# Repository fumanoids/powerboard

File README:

README FOR THE POWER BOARD HARD- AND SOFTWARE RELEASE
           =====================================================

          2016-01-11 FUmanoids' Powerboard Hardware Release v2016

          Copyright (c) 2016 FUmanoids / Freie Universität Berlin
                            All rights reserved

        For full license information, please refer to file LICENCE

Links:
       FUmanoids Homepage                           http://www.fumanoids.de
       FUmanoids on Facebook              http://www.facebook.com/fumanoids
       FUmanoids on Twitter                    http://twitter.com/fumanoids

       RoboCup Homepage                              http://www.robocup.org
       RoboCup Humanoid League Homepage          http://www.tzi.de/humanoid

This is part of the code/hardware release of team FUmanoids, version 2016. 

Our goal by releasing the source code and CAD files of components of our robot
is to provide some insight in humanoid soccer robot development, allowing other
teams to learn from our code and possibly our mistakes, but also to hopefully
encourage them to do the same and release their code as well. Though RoboCup is
a competition, it's also about research and finally to achieve our common goal -
to win against FIFA in 2050 ...

 1. PROJECT STRUCTURE
----------------------

The FUmanoids team has developed several software applications as well as our
own robots. The latter was developed internally and equipped with both
commercially available and self-built electronics.

This release addresses only the custom-built power board used in the FUmanoid
robots.

Neither a compiler, an SDK or CAD software is part of this package. In the
section "Getting Started" you find a list of recommended software to modify or
view the CAD files, to compile the software and to put the binaries onto the
processors.

 1.1 Overview of the package
-----------------------------

The project's root directory is "powerboard" (the board's name).

The directories in the root directory are:

 - bin      -- some useful scripts and programs for building the program and
               documentation
 - obj      -- All binary files of the program go here. This directory will
               be created during code compilation.
 - doc      -- The documentation directory. Here you can find some 
               documentation of the board.
 - src      -- The actual source code.
               Note: The essential parts of the software is pretty well
               documented. Please consider this as a documentation 
               directory as well.
 - hardware -- Here you can find the CAD files for the PCB.

 2. THE POWERBOARD PROJECT
------------------------- 

 2.1 Getting Started
-------------------------

 2.1.1 Software

The software is written in C with two extensions in assembler
(system_mutex_lock() and system_mutex_unlock()).

A compiler for the target hardware is not part of this package but can be picked
based on the user's preferences. We recommend using the arm-none-eabi-toolchain
(including gcc, ld and gdb) which can be found here:

                  https://launchpad.net/gcc-arm-embedded/+download

 2.1.2 Hardware

To view the schematics and layout of this project we recommend using "CadSoft
EAGLE" which can be found at: http://www.cadsoftusa.com/

 2.1.3 Manufacturing

The PCB can be manufactured by most commonly known PCB services. A partlist can
be found in the folder where the schematics reside. But please double check the 
partlist since we cannot guarantee its completeness.

We chose every component on the board to be manually solderable. All you need is
a steady hand. And preferably a rework station.

 2.1.4 Other Prerequisites
 
To flash the target an ARM compatible JTAG is needed.

We recommend using an "JLink" from Segger.
There is numerous software available for all major operating systems supporting
the programmer (Linux, Mac, Windows). 

 2.2 Compiling the Software
---------------------------

To compile for debug run: make
To build a release build: RELEASE=1 make

The common IDE used for development in team FUmanoids is Eclipse/CDT which
is available at http://www.eclipse.org. Therefore we have the corresponding
project files added to our repository, to give an easy start. You can build the
code either by using Eclipse or by shell tools. Both ways are easy.
Other IDEs or editors can of course be used.

The build process generates a .elf file which can be flashed on the target.

 2.2.1 Using Eclipse

If you choose to use Eclipse click File->Import and in the opening window
General->"Existing Project into Workspace" and choose the project's root
directory. Then you can compile the debug or release version of the software.

 2.2.2 Using the shell tools

You can simply run

 make

to compile the code.

 2.3 Flashing the target
------------------------

In order to flash the target you need an JTAG. We recommend using the 
Segger/JLink software to communicate with the JTAG and as tool to download 
code onto the target.

If you have JLinkGDBServer installed you can use 

JLinkGDBServer -if swd
make flash 

to flash the target.

 4. REFERENCES
--------------

The framework used in this software was developed as part of the FUmanoid
project and is used in it's sensor board as well (the project can be found
at http://www.fumanoids.de/hardware/erolf). The Berlin United Racing Team
incorporates a microcontroller board similar to the power board which is
operated by the framework as well.

Many aspects of our work is described in the corresponding theses of our
students, which are available online at http://www.fumanoids.de/publications,
though most of them are in German.

 5. CONTACT
-----------

We'd love to receive feedback, please feel free to contact us by email
at info@fumanoids.de. For information about our team and ongoing progress,
follow us on https://www.facebook.com/fumanoids, https://twitter.com/fumanoids
and http://www.fumanoids.de.

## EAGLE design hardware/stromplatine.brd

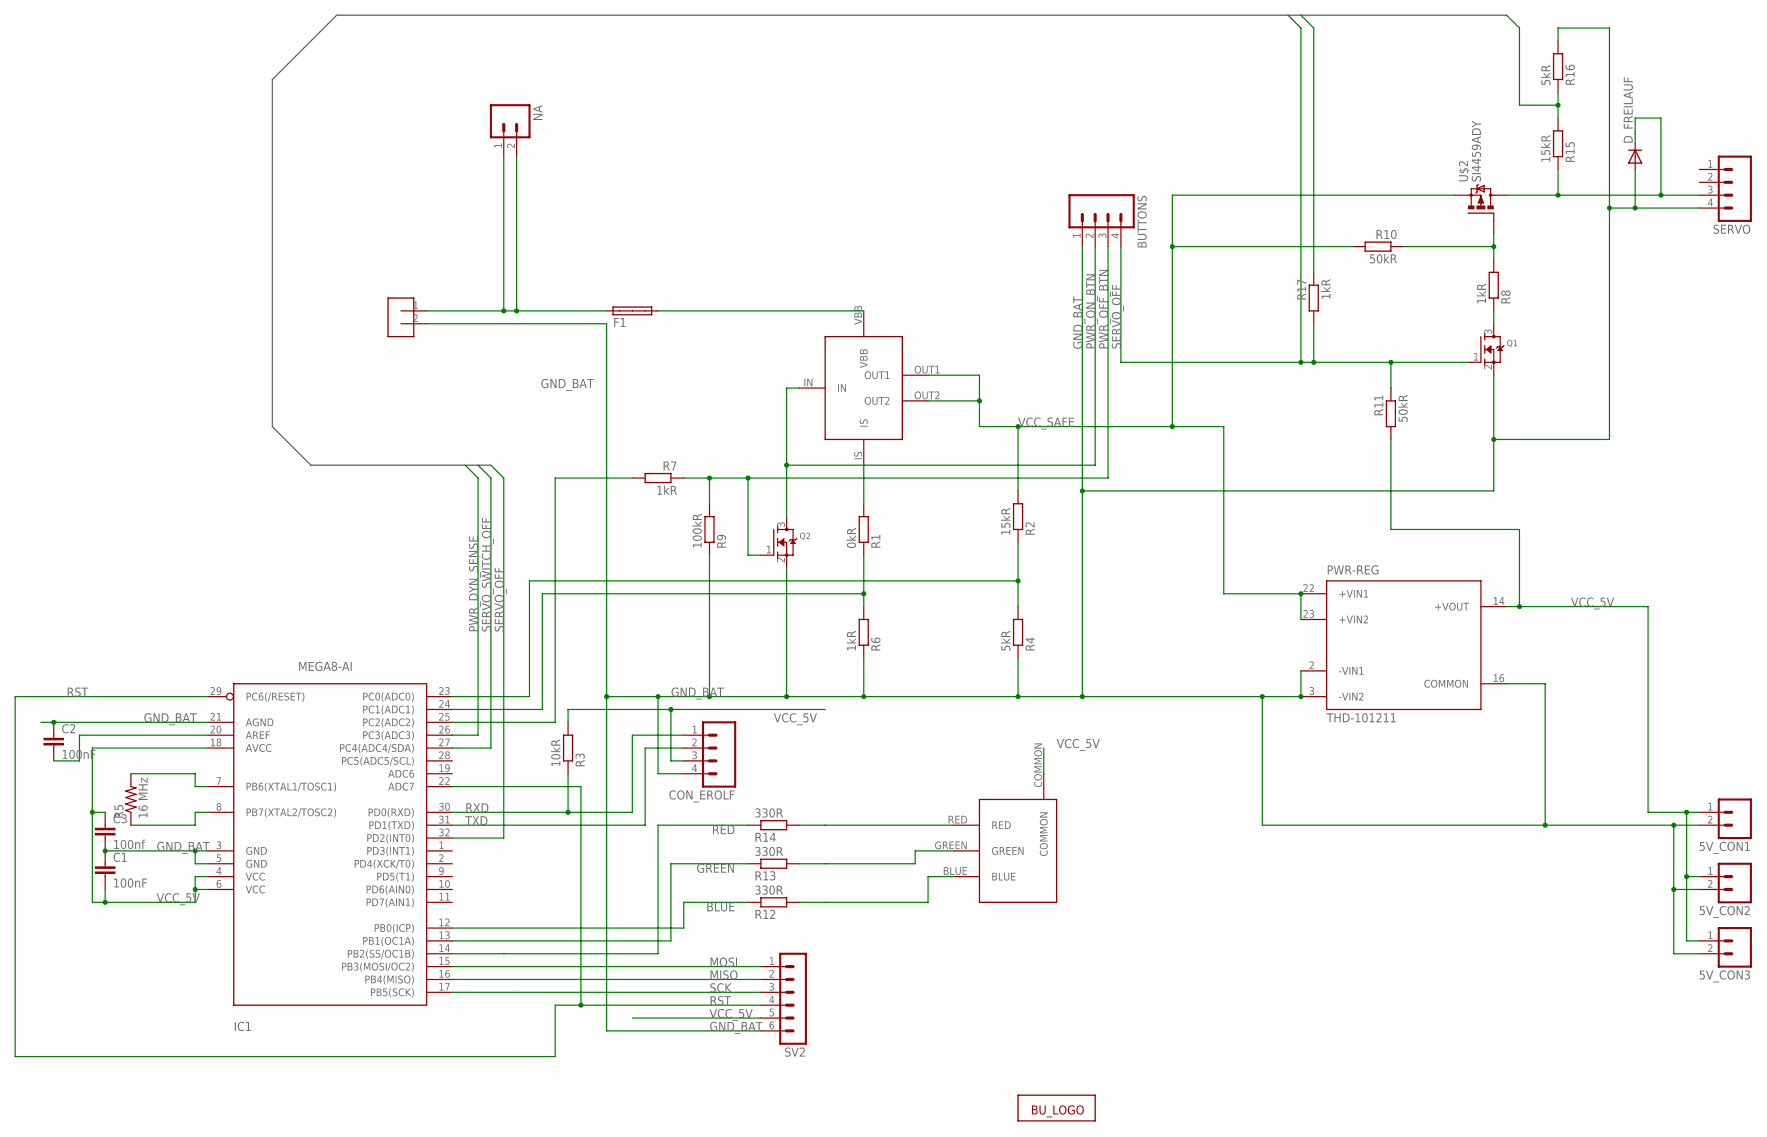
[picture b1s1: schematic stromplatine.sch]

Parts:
5V_CON1, 5V_CON2, 5V_CON3: M02; 02P
BUTTONS: M04; 04P
C1, C2: 100nF; C0805
C3: 100nf; C0805
CON_BAT: STROMSTECKER
CON_EROLF: M04; 04P
D_FREILAUF: DIODE-DO-214AC; DO-214AC
F1: SHK20Q
IC1: MEGA8-AI; TQFP32-08
NA: M02; 02P
PWR-REG: THD-101211; TEN3XXXX
Q1, Q2: MOSFET-NREFLOW; SOT23
R1: 0kR; M0805
R2, R15: 15kR; M0805
R3: 10kR; M0805
R4, R16: 5kR; M0805
R5: 16 MHz; MINI_MELF-0102W
R6, R7, R8, R17: 1kR; M0805
R9: 100kR; M0805
R10, R11: 50kR; M0805
R12, R13, R14: 330R; M0805
SERVO: M04; 04P
SV2: MA06-1
U$1: BTS555; PG-TO218
U$2: SI4459ADY; SO-8
U$3: RGB-LED; 4-PLCC
U$4: LOGO

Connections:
BLUE: IC1.12 (PB0(ICP)), R12.1
GND_BAT: 5V_CON1.2, 5V_CON2.2, 5V_CON3.2, BUTTONS.1, C1.1, C2.1, C3.2, CON_BAT.2, CON_EROLF.4, D_FREILAUF.A, IC1.3 (GND), IC1.5 (GND), IC1.21 (AGND), PWR-REG.2 (-VIN1), PWR-REG.3 (-VIN2), PWR-REG.16 (COMMON), Q1.2 (S), Q2.2 (S), R4.1, R6.1, R9.1, R16.2, SERVO.4, SV2.6
GREEN: IC1.13 (PB1(OC1A)), R13.1
MISO: IC1.16 (PB4(MISO)), SV2.2
MOSI: IC1.15 (PB3(MOSI/OC2)), SV2.1
unnamed: F1.2A, U$1.VBB
unnamed: CON_BAT.1, F1.1A, NA.1, NA.2
unnamed: IC1.7 (PB6(XTAL1/TOSC1)), R5.2
unnamed: R12.2, U$3.BLUE
unnamed: R13.2, U$3.GREEN
unnamed: IC1.8 (PB7(XTAL2/TOSC2)), R5.1
unnamed: IC1.23 (PC0(ADC0)), R2.1, R4.2
unnamed: D_FREILAUF.C, R15.1, SERVO.3, U$2.P5 (D), U$2.P6 (D), U$2.P7 (D), U$2.P8 (D)
unnamed: C2.2, IC1.20 (AREF)
unnamed: R8.2, R10.1, U$2.P4 (G)
unnamed: IC1.24 (PC1(ADC1)), R1.1, R6.2
unnamed: R1.2, U$1.IS
unnamed: Q1.3 (D), R8.1
unnamed: R14.2, U$3.RED
unnamed: IC1.25 (PC2(ADC2)), R7.2
PWR_DYN_SENSE: IC1.26 (PC3(ADC3)), R15.2, R16.1
PWR_OFF_BTN: BUTTONS.3, Q2.1 (G), R7.1, R9.2
PWR_ON_BTN: BUTTONS.2, Q2.3 (D), U$1.IN
RED: IC1.14 (PB2(SS/OC1B)), R14.1
RST: IC1.22 (ADC7), IC1.29 (PC6(/RESET)), SV2.4
RXD: CON_EROLF.1, IC1.30 (PD0(RXD)), R3.1
SCK: IC1.17 (PB5(SCK)), SV2.3
SERVO_OFF: BUTTONS.4, IC1.32 (PD2(INT0)), Q1.1 (G), R11.1, R17.2
SERVO_SWITCH_OFF: IC1.27 (PC4(ADC4/SDA)), R17.1
TXD: CON_EROLF.2, IC1.31 (PD1(TXD))
VCC_5V: 5V_CON1.1, 5V_CON2.1, 5V_CON3.1, C1.2, C3.1, CON_EROLF.3, IC1.4 (VCC), IC1.6 (VCC), IC1.18 (AVCC), PWR-REG.14 (+VOUT), R3.2, R11.2, SV2.5, U$3.COMMON
VCC_SAFE: PWR-REG.22 (+VIN1), PWR-REG.23 (+VIN2), R2.2, R10.2, U$1.OUT1, U$1.OUT2, U$2.P1 (S), U$2.P2 (S), U$2.P3 (S)

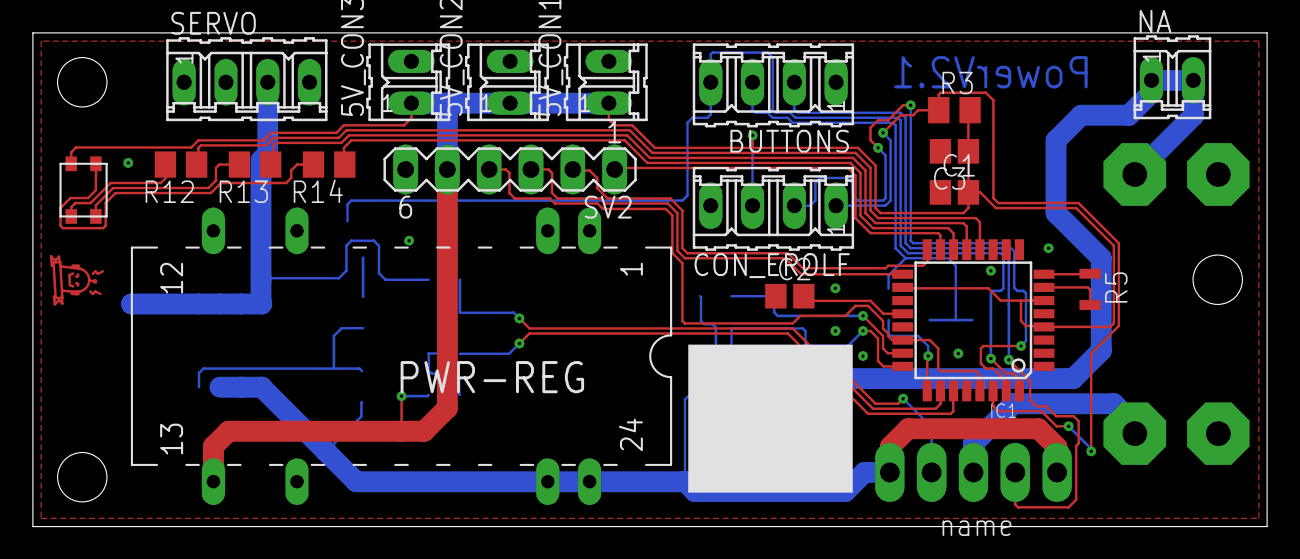
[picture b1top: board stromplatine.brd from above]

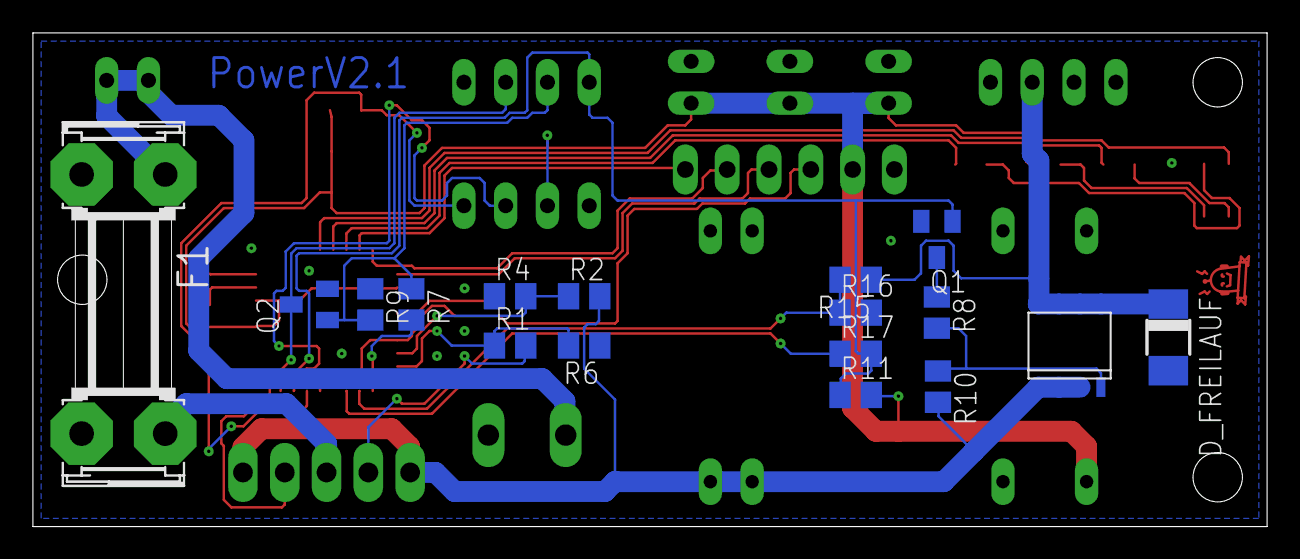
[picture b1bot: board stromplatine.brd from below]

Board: 2 copper layers, 75.0 x 30.0 mm, 39 parts (17 on the bottom side), 32 nets.

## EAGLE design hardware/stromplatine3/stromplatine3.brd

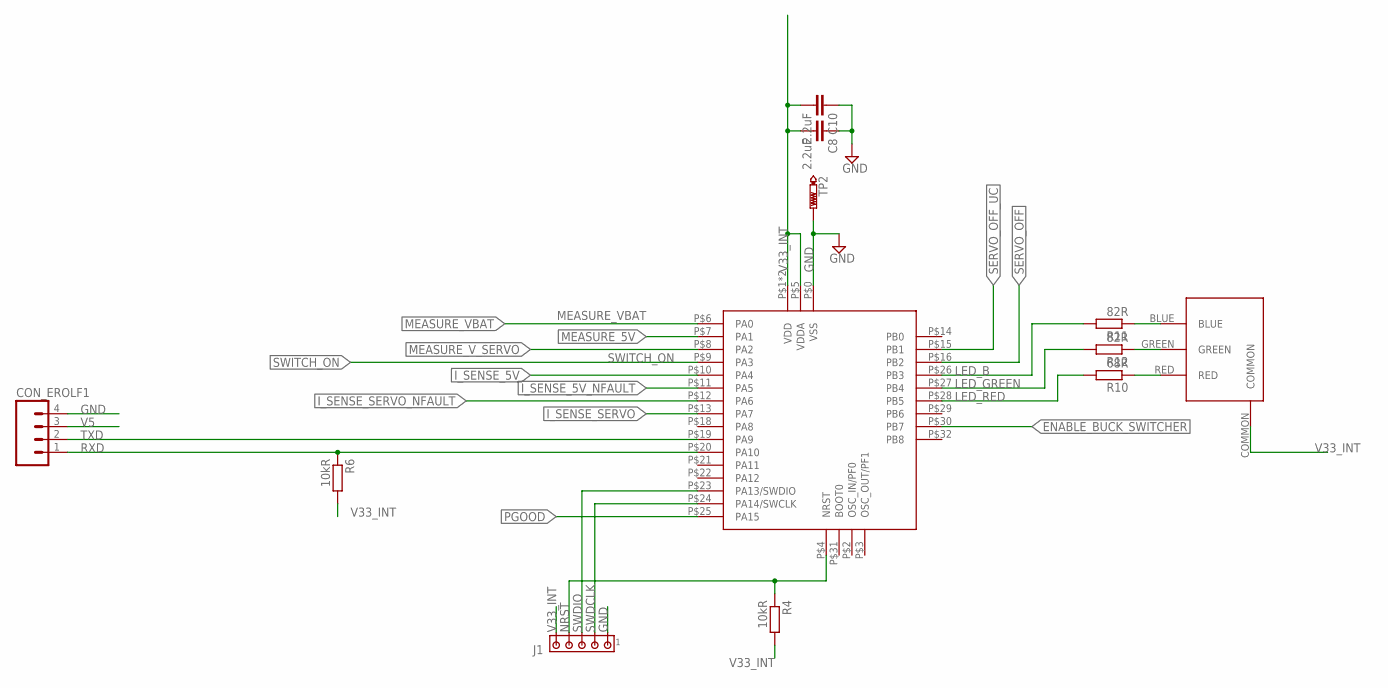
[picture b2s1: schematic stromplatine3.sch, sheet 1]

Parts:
C8, C10: 2.2uF; C0402
CON_EROLF1: M04; 04P
J1: MTA05-100; 10X05MTA
R4, R6: 10kR; R0603
R10: 68R; R0603
R11, R12: 82R; R0603
TP2: PTR1B1,27; B1,27
U$1: STM32F051K8; UFQFPN32
U$3: RGB-LED; 4-PLCC

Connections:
ENABLE_BUCK_SWITCHER: U$1.P$30 (PB7); also elsewhere on the board
GND: C8.1, C10.1, CON_EROLF1.4, J1.1, TP2.TP, U$1.P$0 (VSS); also elsewhere on the board
I_SENSE_5V: U$1.P$10 (PA4); also elsewhere on the board
I_SENSE_5V_NFAULT: U$1.P$11 (PA5); also elsewhere on the board
I_SENSE_SERVO: U$1.P$13 (PA7); also elsewhere on the board
I_SENSE_SERVO_NFAULT: U$1.P$12 (PA6); also elsewhere on the board
LED_B: R11.2, U$1.P$26 (PB3)
LED_GREEN: R12.2, U$1.P$27 (PB4)
LED_RED: R10.2, U$1.P$28 (PB5)
MEASURE_5V: U$1.P$7 (PA1); also elsewhere on the board
MEASURE_VBAT: U$1.P$6 (PA0); also elsewhere on the board
MEASURE_V_SERVO: U$1.P$8 (PA2); also elsewhere on the board
unnamed: R10.1, U$3.RED
unnamed: R12.1, U$3.GREEN
unnamed: R11.1, U$3.BLUE
NRST: J1.4, R4.1, U$1.P$4 (NRST)
PGOOD: U$1.P$25 (PA15)
RXD: CON_EROLF1.1, R6.1, U$1.P$20 (PA10)
SERVO_OFF: U$1.P$16 (PB2); also elsewhere on the board
SERVO_OFF_UC: U$1.P$15 (PB1)
SWDCLK: J1.2, U$1.P$24 (PA14/SWCLK)
SWDIO: J1.3, U$1.P$23 (PA13/SWDIO)
SWITCH_ON: U$1.P$9 (PA3); also elsewhere on the board
TXD: CON_EROLF1.2, U$1.P$19 (PA9)
V5: CON_EROLF1.3; also elsewhere on the board
V33_INT: C8.2, C10.2, J1.5, R4.2, R6.2, U$1.P$1 (VDD), U$1.P$5 (VDDA), U$1.P$17 (VDD), U$3.COMMON; also elsewhere on the board

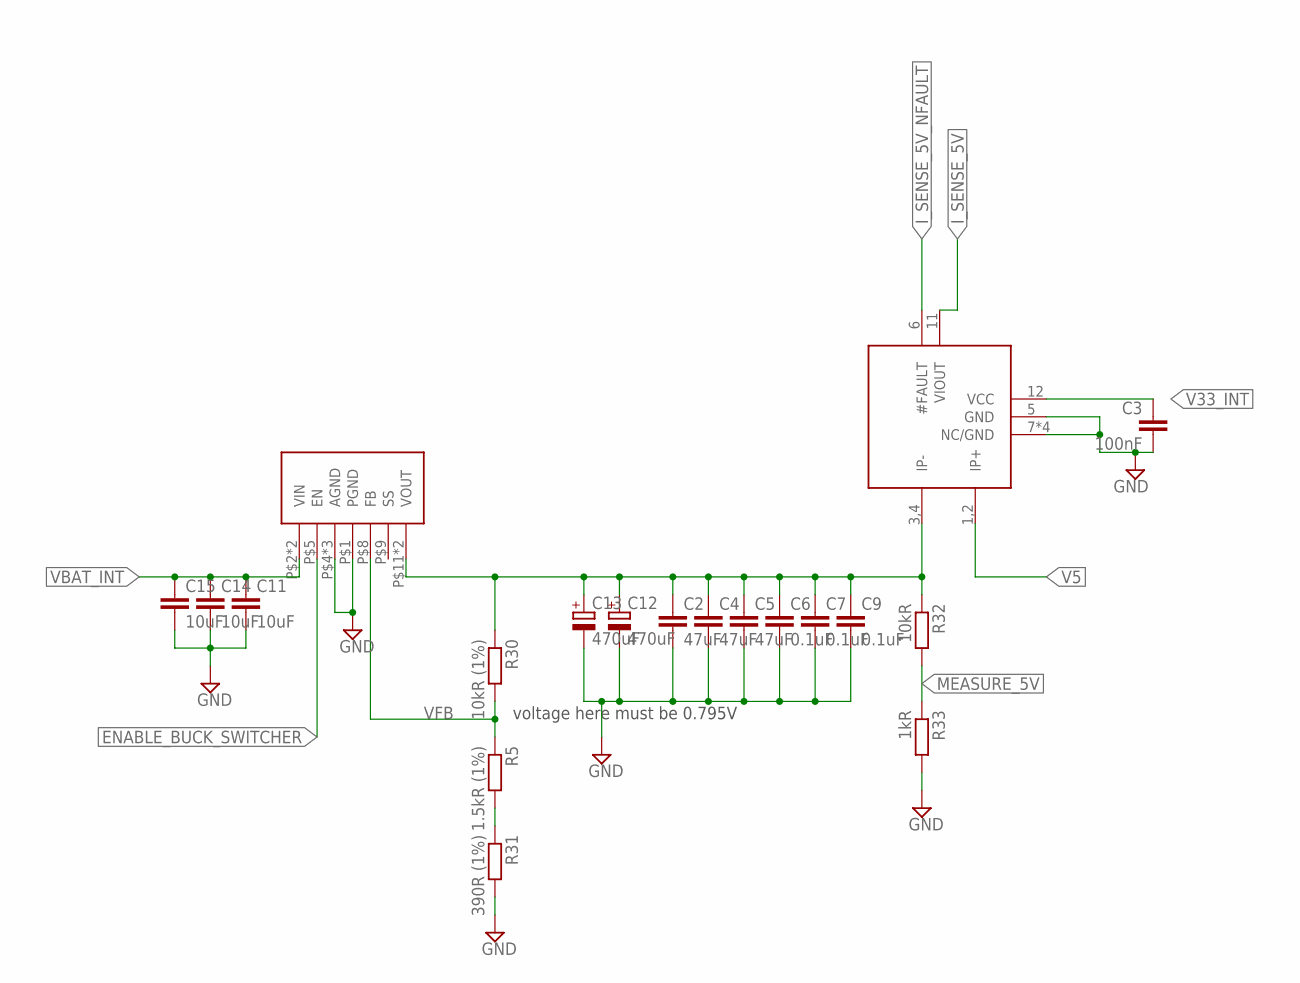
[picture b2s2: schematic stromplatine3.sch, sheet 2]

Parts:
C2, C4, C5: 47uF; C1206
C3: 100nF; C0402
C6, C7, C9: 0.1uF; C0603
C11, C14, C15: 10uF; C1206; DIGIKEY 587-1353-1-ND
C12, C13: 470uF; 175TMP-0810; DIGIKEY 493-3771-1-ND
R5: 1.5kR (1%); R0603
R30: 10kR (1%); R0603
R31: 390R (1%); R0603
R32: 10kR; R0603
R33: 1kR; R0603
U$10: ACS711; QFN-12-EX
U$11: LMZ12010; TZA11A

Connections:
ENABLE_BUCK_SWITCHER: U$11.P$5 (EN); also elsewhere on the board
GND: C2.2, C3.2, C4.2, C5.2, C6.2, C7.2, C9.2, C11.2, C12.-, C13.-, C14.2, C15.2, R31.2, R33.2, U$10.5 (GND), U$10.7 (NC/GND), U$10.8 (NC/GND), U$10.9 (NC/GND), U$10.10 (NC/GND), U$11.P$1 (PGND), U$11.P$4 (AGND), U$11.P$6 (AGND), U$11.P$7 (AGND); also elsewhere on the board
I_SENSE_5V: U$10.11 (VIOUT); also elsewhere on the board
I_SENSE_5V_NFAULT: U$10.6 (#FAULT); also elsewhere on the board
MEASURE_5V: R32.2, R33.1; also elsewhere on the board
unnamed: R5.2, R31.1
unnamed: C2.1, C4.1, C5.1, C6.1, C7.1, C9.1, C12.+, C13.+, R30.1, R32.1, U$10.3,4 (IP-), U$11.P$11 (VOUT), U$11.P$12 (VOUT)
V5: U$10.1,2 (IP+); also elsewhere on the board
V33_INT: C3.1, U$10.12 (VCC); also elsewhere on the board
VBAT_INT: C11.1, C14.1, C15.1, U$11.P$2 (VIN), U$11.P$3 (VIN); also elsewhere on the board
VFB: R5.1, R30.2, U$11.P$8 (FB)

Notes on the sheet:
voltage here must be 0.795V

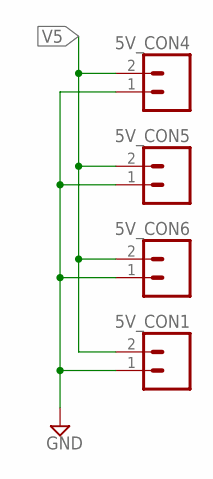
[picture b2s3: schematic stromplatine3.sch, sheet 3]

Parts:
5V_CON1, 5V_CON4, 5V_CON5, 5V_CON6: M02; 02P

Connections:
GND: 5V_CON1.1, 5V_CON4.1, 5V_CON5.1, 5V_CON6.1; also elsewhere on the board
V5: 5V_CON1.2, 5V_CON4.2, 5V_CON5.2, 5V_CON6.2; also elsewhere on the board

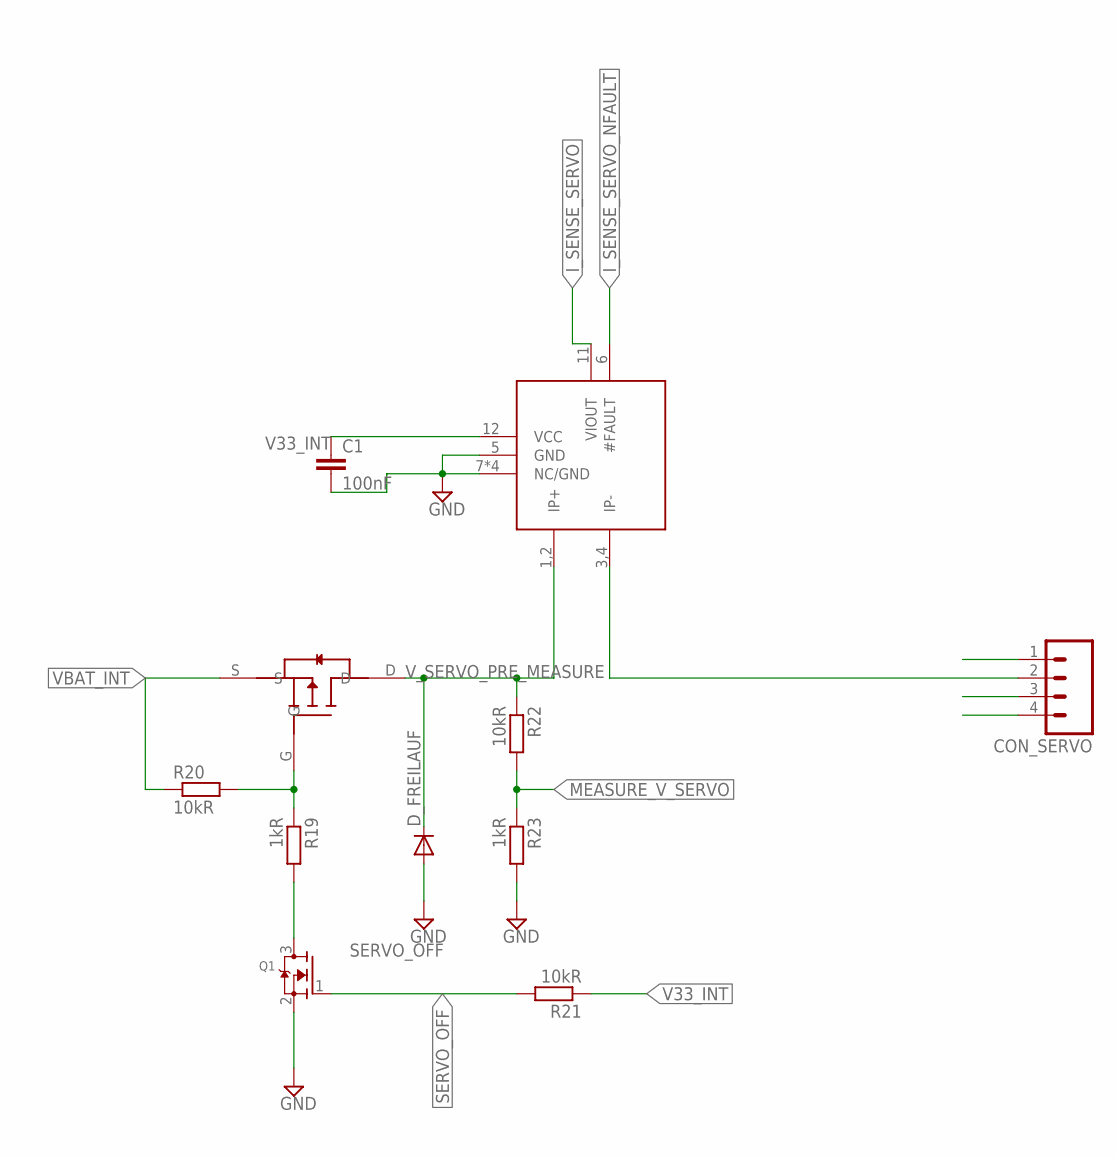
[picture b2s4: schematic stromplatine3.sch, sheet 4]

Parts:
C1: 100nF; C0402
CON_SERVO: M04; 04P
D_FREILAUF: DIODE-DO-214AC; DO-214AC
Q1: MOSFET-NREFLOW; SOT23
R19, R23: 1kR; R0603
R20, R21, R22: 10kR; R0603
U$6: ACS711; QFN-12-EX
U$7: MOSFET/AOD417; TO-252

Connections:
GND: C1.2, CON_SERVO.1, D_FREILAUF.A, Q1.2 (S), R23.2, U$6.5 (GND), U$6.7 (NC/GND), U$6.8 (NC/GND), U$6.9 (NC/GND), U$6.10 (NC/GND); also elsewhere on the board
I_SENSE_SERVO: U$6.11 (VIOUT); also elsewhere on the board
I_SENSE_SERVO_NFAULT: U$6.6 (#FAULT); also elsewhere on the board
MEASURE_V_SERVO: R22.2, R23.1; also elsewhere on the board
unnamed: Q1.3 (D), R19.2
unnamed: R19.1, R20.2, U$7.G
RS485_SERVO_A: CON_SERVO.3
RS485_SERVO_B: CON_SERVO.4
SERVO_OFF: Q1.1 (G), R21.2; also elsewhere on the board
V33_INT: C1.1, R21.1, U$6.12 (VCC); also elsewhere on the board
VBAT_INT: R20.1, U$7.S; also elsewhere on the board
V_SERVO: CON_SERVO.2, U$6.3,4 (IP-)
V_SERVO_PRE_MEASURE: D_FREILAUF.C, R22.1, U$6.1,2 (IP+), U$7.D

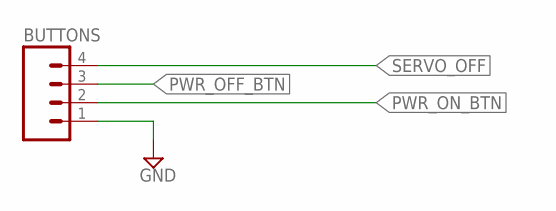
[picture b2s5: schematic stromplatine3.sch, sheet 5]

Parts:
BUTTONS: M04; 04P

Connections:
GND: BUTTONS.1; also elsewhere on the board
PWR_OFF_BTN: BUTTONS.3; also elsewhere on the board
PWR_ON_BTN: BUTTONS.2; also elsewhere on the board
SERVO_OFF: BUTTONS.4; also elsewhere on the board

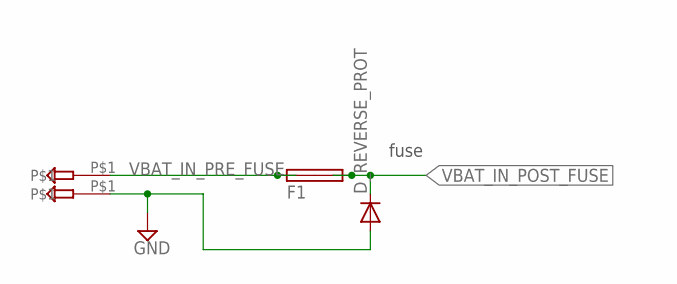
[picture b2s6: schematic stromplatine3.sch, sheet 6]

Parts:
D_REVERSE_PROT: DIODE-DO-214AC; DO-214AC
F1: SHK20Q
U$8, U$9: TP

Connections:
GND: D_REVERSE_PROT.A, U$9.P$1; also elsewhere on the board
VBAT_IN_POST_FUSE: D_REVERSE_PROT.C, F1.2A, F1.2B; also elsewhere on the board
VBAT_IN_PRE_FUSE: F1.1A, F1.1B, U$8.P$1

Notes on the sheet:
fuse

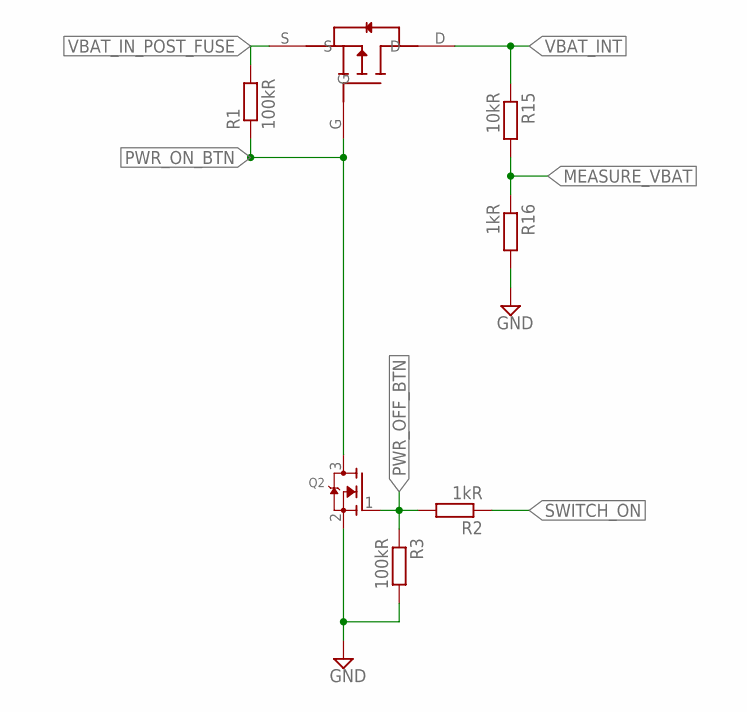
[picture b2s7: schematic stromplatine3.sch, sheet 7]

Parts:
Q2: MOSFET-NREFLOW; SOT23
R1, R3: 100kR; R0603
R2, R16: 1kR; R0603
R15: 10kR; R0603
U$4: MOSFET/AOD417; TO-252

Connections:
GND: Q2.2 (S), R3.2, R16.2; also elsewhere on the board
MEASURE_VBAT: R15.2, R16.1; also elsewhere on the board
PWR_OFF_BTN: Q2.1 (G), R2.2, R3.1; also elsewhere on the board
PWR_ON_BTN: Q2.3 (D), R1.1, U$4.G; also elsewhere on the board
SWITCH_ON: R2.1; also elsewhere on the board
VBAT_INT: R15.1, U$4.D; also elsewhere on the board
VBAT_IN_POST_FUSE: R1.2, U$4.S; also elsewhere on the board

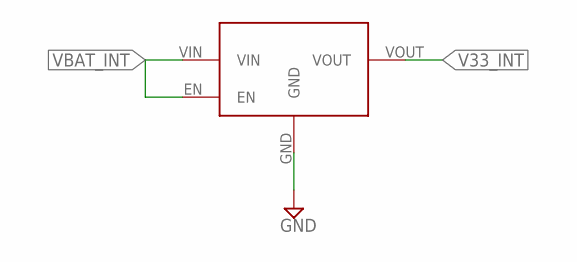
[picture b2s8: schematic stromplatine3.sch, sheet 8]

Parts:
U$2: LDO/AP2204; SOT-23-5

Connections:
GND: U$2.GND; also elsewhere on the board
V33_INT: U$2.VOUT; also elsewhere on the board
VBAT_INT: U$2.EN, U$2.VIN; also elsewhere on the board

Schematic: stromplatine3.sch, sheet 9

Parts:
U$5: LOGO

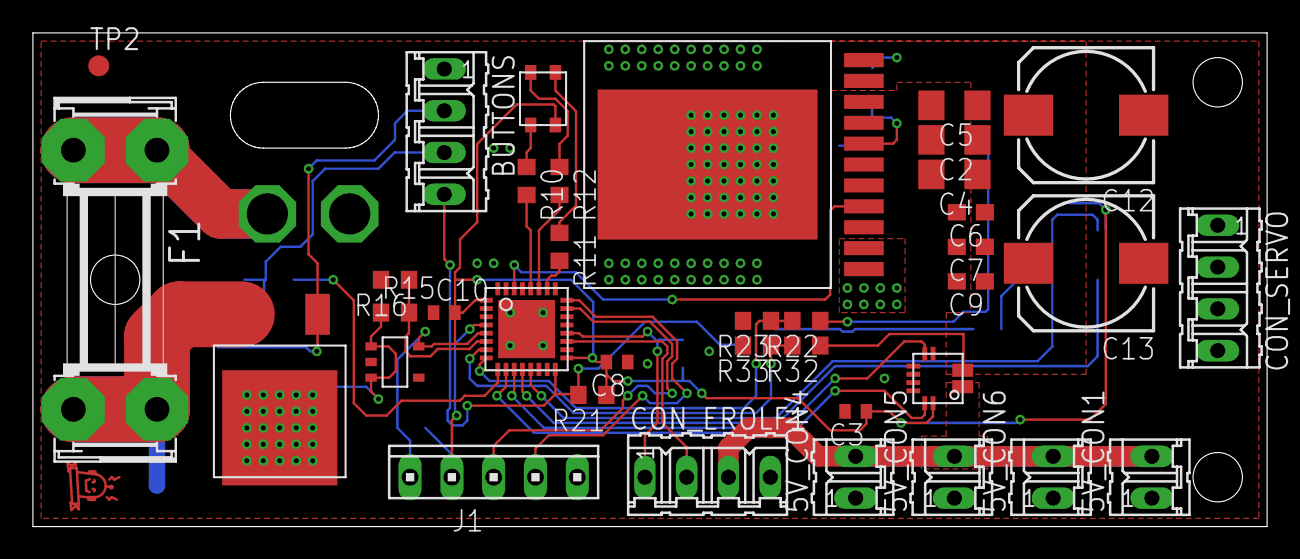
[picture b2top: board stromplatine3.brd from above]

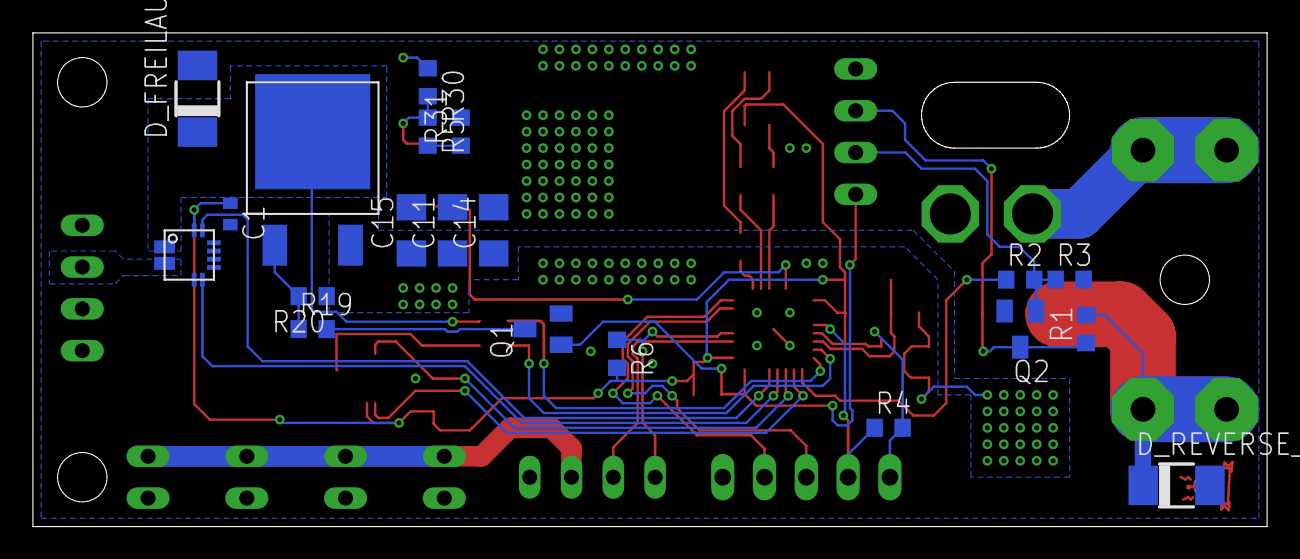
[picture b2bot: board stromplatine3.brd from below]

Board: 2 copper layers, 75.0 x 30.0 mm, 60 parts (20 on the bottom side), 36 nets.

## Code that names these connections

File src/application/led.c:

#include "led.h"
#include <flawless/init/systemInitializer.h>
#include <flawless/core/msg_msgPump.h>
#include <flawless/config/msgIDs.h>
#include <flawless/timer/swTimer.h>

#include <avr/io.h>
#include <avr/eeprom.h>
#include <avr/interrupt.h>
#include <util/delay.h>

#define LED_PORT      (PORTB)
#define LED_DIRECTION (DDRB)
#define LED_BLUE      (PB0)
#define LED_GREEN     (PB1)
#define LED_RED       (PB2)



static void onBatteryVoltageReady(msgPump_MsgID_t, const void *);


void led_init();
MODULE_INIT_FUNCTION(led, 0, led_init)
void led_init()
{
	// set pins to output
	LED_DIRECTION |= 1 << LED_RED;
	LED_DIRECTION |= 1 << LED_GREEN;
	LED_DIRECTION |= 1 << LED_BLUE;
	LED_PORT |= (1 << LED_RED);
	LED_PORT |= (1 << LED_GREEN);
	LED_PORT |= (1 << LED_BLUE);

	TCCR1A = 0U;
	TCCR1B = 0U;

	ICR1L = 0xff;
	ICR1H = 0x00;

	/* set OC1A/B on compare match (fast PWM-mode with ICR1 as TOP) no prescaler */
	TCCR1A |= (1 << COM1A1) | (1 << COM1A0) | (1 << COM1B1) | (1 << COM1B0);
	TCCR1A |=  (1 << WGM11);
	TCCR1B |=  (1 << WGM12) | (1 << WGM13) | (1 << CS10);
}

void led_init2();
MODULE_INIT_FUNCTION(led2, 9, led_init2)
void led_init2()
{
	led_setColor(64, 64);
	msgPump_registerOnMessage(MSG_ID_RELATIVE_BATTERY_VOLTAGE, &onBatteryVoltageReady);
}


static void onBatteryVoltageReady(msgPump_MsgID_t i_msgID, const void *i_data)
{
	const uint8_t value = *((const uint8_t*) i_data);

	uint8_t green;
	uint8_t red;

	if (value >= 128)
	{
		green = 0xff;
		red   = 2 * (255 - value);
	} else
	{
		red = 0xff;
		green   = 2 * value;
	}

	led_setColor(red, green);
}

void led_setColor(uint8_t red, uint8_t green)
{
	OCR1BL = (red & 0x00ff);
	OCR1AL = (green & 0x00ff);
}

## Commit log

2014-02-13 code release 2014
2016-01-11 Yeyyy the new version of the power board... woooohoooo
2016-01-11 oh boy... time passes quickly
